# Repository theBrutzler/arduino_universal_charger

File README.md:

# arduino_universal_charger
 a esp32 arduino based charger

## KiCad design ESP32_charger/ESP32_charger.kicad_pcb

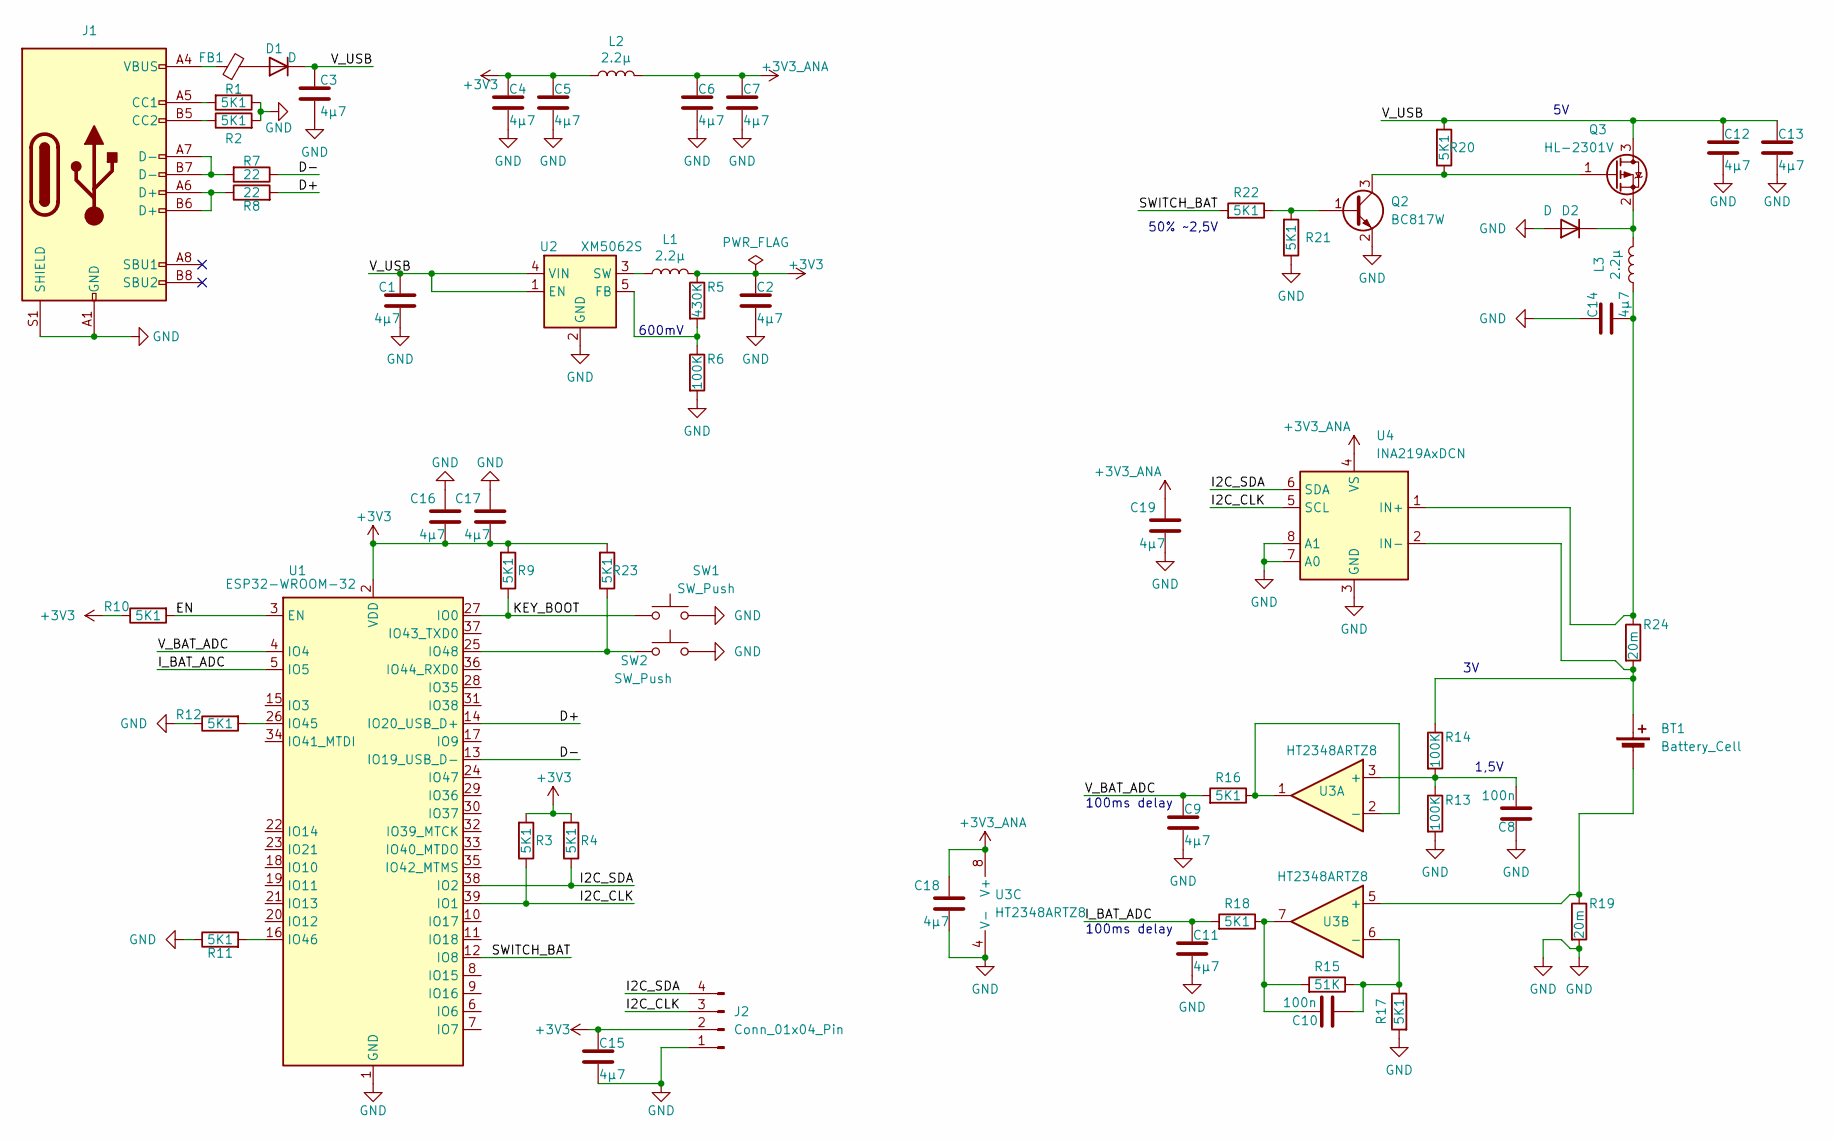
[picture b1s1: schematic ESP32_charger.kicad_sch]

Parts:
BT1: Battery_Cell; PinHeader_1x02_P2.54mm_Vertical
C1, C2, C3, C4, C5, C6, C7, C9, C11, C12, C13, C14, C15, C16, C17, C18, C19: 4µ7; C_1206_3216Metric; LCSC C282809
C8, C10: 100n; C_0603_1608Metric
D1, D2: D; Nexperia_CFP3_SOD-123W; LCSC C5120763
FB1: FerriteBead_Small; L_0805_2012Metric; LCSC C963878
J1: USB_C_Receptacle_USB2.0_16P; USB_C_Receptacle_HRO_TYPE-C-31-M-12; LCSC C165948
J2: Conn_01x04_Pin; PinHeader_1x04_P2.54mm_Vertical
L1, L2, L3: 2.2µ; L_1210_3225Metric_Pad1.42x2.65mm_HandSolder; LCSC C3002559
Q2: BC817W; SOT-323_SC-70
Q3: HL-2301V; SOT-23; LCSC C7499856
R1, R2, R3, R4, R9, R10, R11, R12, R16, R17, R18, R20, R21, R22, R23: 5K1; R_0603_1608Metric; LCSC C26000
R5: 430K; R_0603_1608Metric; LCSC C25969
R6, R13, R14: 100K; R_0603_1608Metric; LCSC C15458
R7, R8: 22; R_0603_1608Metric; LCSC C1203
R15: 51K; R_0603_1608Metric; LCSC C26000
R19, R24: 20m; R_1206_3216Metric; LCSC C516459
SW1, SW2: SW_Push; SW_SPST_CK_RS282G05A3
U1: ESP32-WROOM-32; ESP32-S3-WROOM-1; LCSC C2913201
U2: XM5062S; SOT-23-5; LCSC C2924930
U3: HT2348ARTZ8; TSOT-23-8; LCSC C5143016
U4: INA219AxDCN; SOT-23-8

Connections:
+3V3: C2.1, C4.1, C5.1, C15.1, C16.2, C17.2, J2.2, L1.2, L2.1, R3.2, R4.2, R5.1, R9.2, R10.1, R23.2, U1.2 (VDD)
+3V3_ANA: C6.1, C7.1, C18.1, C19.1, L2.2, U3.8 (V+), U4.4 (VS)
/D+: R8.2, U1.14 (IO20_USB_D+)
/D-: R7.1, U1.13 (IO19_USB_D-)
/EN: R10.2, U1.3 (EN)
/I2C_CLK: J2.3, R3.1, U1.39 (IO1), U4.5 (SCL)
/I2C_SDA: J2.4, R4.1, U1.38 (IO2), U4.6 (SDA)
/I_BAT_ADC: C11.1, R18.2, U1.5 (IO5)
/KEY_BOOT: R9.1, SW1.1, U1.27 (IO0)
/SWITCH_BAT: R22.2, U1.12 (IO8)
/V_BAT_ADC: C9.1, R16.2, U1.4 (IO4)
/V_USB: C1.1, C3.1, C12.1, C13.1, D1.1 (K), Q3.3 (D), R20.2, U2.1 (EN), U2.4 (VIN)
GND: C1.2, C2.2, C3.2, C4.2, C5.2, C6.2, C7.2, C8.1, C9.2, C11.2, C12.2, C13.2, C14.1, C15.2, C16.1, C17.1, C18.2, C19.2, D2.2 (A), J1.A1 (GND), J1.A12 (GND), J1.B1 (GND), J1.B12 (GND), J1.S1 (SHIELD), J2.1, Q2.2 (E), R1.1, R2.2, R6.2, R11.1, R12.1, R13.2, R17.2, R19.2, R21.1, SW1.2, SW2.2, U1.1 (GND), U1.40 (GND), U1.41 (GND), U2.2 (GND), U3.4 (V-), U4.3 (GND), U4.7 (A0), U4.8 (A1)
unnamed: BT1.1 (+), R14.1, R24.2, U4.2 (IN-)
unnamed: BT1.2 (-), R19.1, U3.5 (+)
unnamed: C10.2, R15.2, R18.1, U3.7
unnamed: D1.2 (A), FB1.2
unnamed: D2.1 (K), L3.2, Q3.2 (S)
unnamed: FB1.1, J1.A4 (VBUS), J1.A9 (VBUS), J1.B4 (VBUS), J1.B9 (VBUS)
unnamed: J1.A5 (CC1), R1.2
unnamed: J1.B5 (CC2), R2.1
unnamed: J1.A6 (D+), J1.B6 (D+), R8.1
unnamed: J1.A7 (D-), J1.B7 (D-), R7.2
unnamed: Q2.1 (B), R21.2, R22.1
unnamed: Q2.3 (C), Q3.1 (G), R20.1
unnamed: R12.2, U1.26 (IO45)
unnamed: R11.2, U1.16 (IO46)
unnamed: R23.1, SW2.1, U1.25 (IO48)
unnamed: R5.2, R6.1, U2.5 (FB)
unnamed: L1.1, U2.3 (SW)
unnamed: C8.2, R13.1, R14.2, U3.3 (+)
unnamed: R16.1, U3.1, U3.2 (-)
unnamed: C10.1, R15.1, R17.1, U3.6 (-)
unnamed: C14.2, L3.1, R24.1, U4.1 (IN+)

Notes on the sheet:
1,5V
50% ~2,5V
100ms delay
600mV

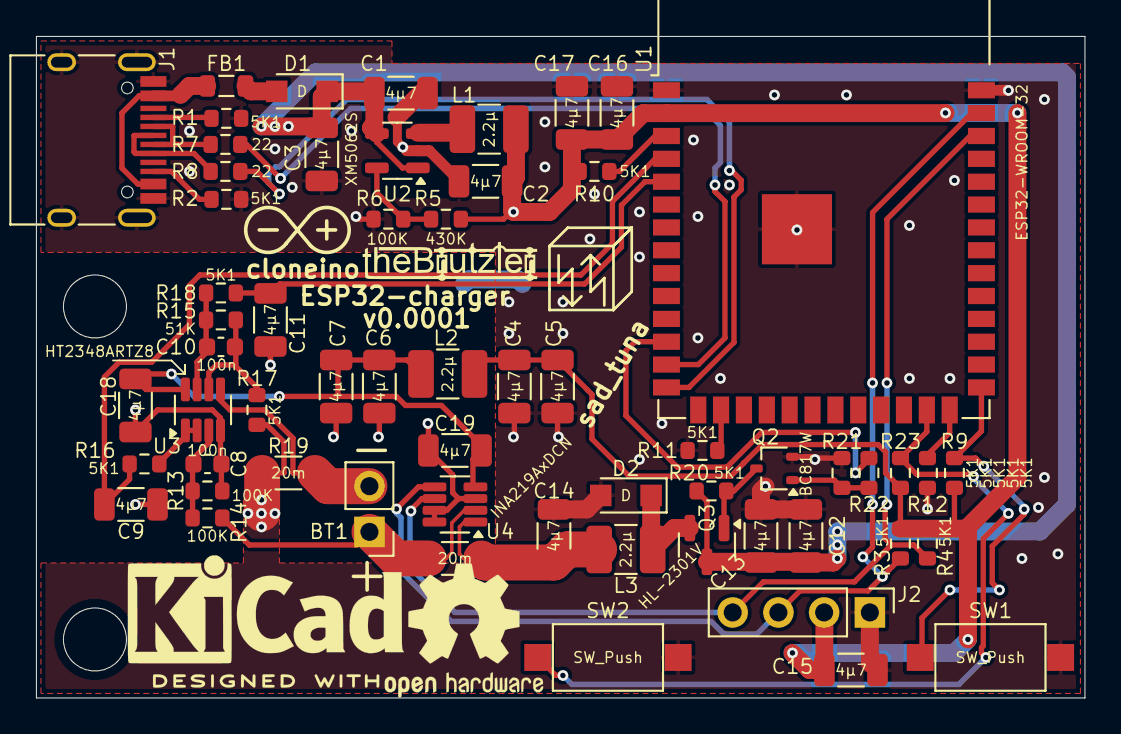
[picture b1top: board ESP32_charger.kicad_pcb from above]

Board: 2 copper layers, 58.2 x 36.8 mm, 61 parts (0 on the bottom side), 34 nets.

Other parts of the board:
SM3: SYM_Arrow45_Tiny; Symbol_kurzschlussblog

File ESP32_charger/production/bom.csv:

Designator,Footprint,Quantity,Value,LCSC Part #
BT1,PinHeader_1x02_P2.54mm_Vertical,1,Battery_Cell,
"C1, C11, C12, C13, C14, C15, C16, C17, C18, C19, C2, C3, C4, C5, C6, C7, C9",1206,17,4µ7,C282809
"C10, C8",0603,2,100n,
"D1, D2",Nexperia_CFP3_SOD-123W,2,D,C5120763
FB1,0805,1,FerriteBead_Small,C963878
J1,USB_C_Receptacle_HRO_TYPE-C-31-M-12,1,USB_C_Receptacle_USB2.0_16P,C165948
J2,PinHeader_1x04_P2.54mm_Vertical,1,Conn_01x04_Pin,
"L1, L2, L3",1210,3,2.2µ,C3002559
Q2,SOT-323_SC-70,1,BC817W,
Q3,SOT-23,1,HL-2301V,C7499856
"R1, R10, R11, R12, R16, R17, R18, R2, R20, R21, R22, R23, R3, R4, R9",0603,15,5K1,C26000
"R13, R14, R6",0603,3,100K,C15458
R15,0603,1,51K,C26000
"R19, R24",1206,2,20m,C516459
R5,0603,1,430K,C25969
"R7, R8",0603,2,22,C1203
SW1,SW_SPST_CK_RS282G05A3,1,SW_Push,
SW2,SW_SPST_CK_RS282G05A3,1,SW_Push,C913791
U1,ESP32-S3-WROOM-1,1,ESP32-WROOM-32,C2913201
U2,SOT-23-5,1,XM5062S,C2924930
U3,TSOT-23-8,1,HT2348ARTZ8,C5143016
U4,SOT-23-8,1,INA219AxDCN,

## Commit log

2024-09-17 initial upload
    todo:
    * silkscreen
    * clear dlc errors
2024-09-17 add schematic
2024-09-19 update to order version
    placed silkscreen
    placed logos
    add 3d models
    generate 3d model
2024-09-19 update production files
2024-09-19 add mounting holes and tuna logo
2024-11-07 update html bom
